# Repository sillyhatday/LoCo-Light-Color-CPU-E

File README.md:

# Introduction

As you may know, there are different revision CPUs that came in the GBC. All are compatible with each other except the last revision. This project allows for the use of that version inside of a Gameboy Light form factor.

The final revision CGB was cost cut as much as possible, Nintendo removed as much as they could from the console. All filtering removed by Nintendo has been removed from this also.

There is a bit of shell trimming required when assembling. The front face of the shell requires trimming for the screen like all IPS screen replacements. There is some trimming needed around the click wheel also as it's bigger than the orginal contrast wheel on a Light console. I'll document this when I have completed the build.

>[!IMPORTANT]
>This version only works with CGB-CPU-06 revisions, known as CPU-E

>[!NOTE]
>Limited new parts are needed, the 2.5v regulator and toggle wheel. I could have used the regulator from the donor, it just has an odd pin out. Such a small part is easy to loose or damage, so I went with a new part with a standard pin out. Everything else is the same as the original version.

Here is Natalie's origiinal readme with my images.

# LoCo (Light Color) - NatalieTheNerd

LoCo = Light Color. This project allows you to put a Game Boy Color in a Game Boy Light shell. Full Light colour PCB using the original parts. This board is made with modern screen kits in mind meaning it does not have the voltage rails for the original screen.

**ORDER AT 1MM WITH ENIG**

You can support me on Ko-Fi or by buying the board directly from me [my store](https://nataliethenerd.com/collections/all)

I also occasionally sell pre built PCBs on my store.

## Building

> [!WARNING]
> I am not responsible for your skill issues!

>[!TIP]
>Some details that will need your atention during assembly are [here](SHELLTRIMMING.md)

This board uses all the parts of an original Game Boy Color minus the IR and original screen circuit. Most parts are in the same spot, however if you are having trouble you can check the [interactive BOM](https://nataliethenerd.github.io/loco.html)

The thumbwheel circuit can be connected to an OSD screen to control brightness. The two touch pad wires and be connected to the pads labelled ↑↓ on the back top left side of the board. The select, A and B pads are easy connection pads for the screen also. 

**My recommendations** 

- New power regulator like my [Safer Charge DC](https://nataliethenerd.com/products/safer-charge-dc)
- [Q5 OSD Game Boy Color screen](https://s.click.aliexpress.com/e/_DmvDS95). The OSD allows you to move the screen

**New parts**

- [Thumbwheel](https://s.click.aliexpress.com/e/_DFcsKf1)

## Thanks
- Hozy for the pushing me to do the first ever Light Color
- Console and Casks for the thumbwheel circuit

## Follow me

If you are into Game Boy modding or retro gaming, please consider using code "NatalieTheNerd" at:

• [Retro Modding](http://RetroModding.com) 

• [Retro Game Repair Shop](http://RetroGameRepairShop.com) 

• [Extreme Rate](http://ExtremeRate.com)

**My socials**

• [Twitter](https://twitter.com/natalie_thenerd) 

• [BlueSky](https://bsky.app/profile/nataliethenerd.com) 

• [Instagram](https://www.instagram.com/natalie.thenerd/) 

• [Modded Gameboy Club](https://moddedgameboy.club/) - a club dedicated to the modification of Game Boys, freely sharing resources

## License

Please do not remove my logo, website and name.

The CC BY-SA 4.0 (Creative Commons Attribution-ShareAlike 4.0 International) license allows you to:

1. **Share** - Copy and redistribute the material in any medium or format.
2. **Adapt** - Remix, transform, and build upon the material for any purpose, even commercially.

### Conditions:

- **Attribution** - You must give appropriate credit, provide a link to the license, and indicate if changes were made. You may do so in any reasonable manner, but not in any way that suggests the licensor endorses you or your use.
- **ShareAlike** - If you remix, transform, or build upon the material, you must distribute your contributions under the same license as the original.

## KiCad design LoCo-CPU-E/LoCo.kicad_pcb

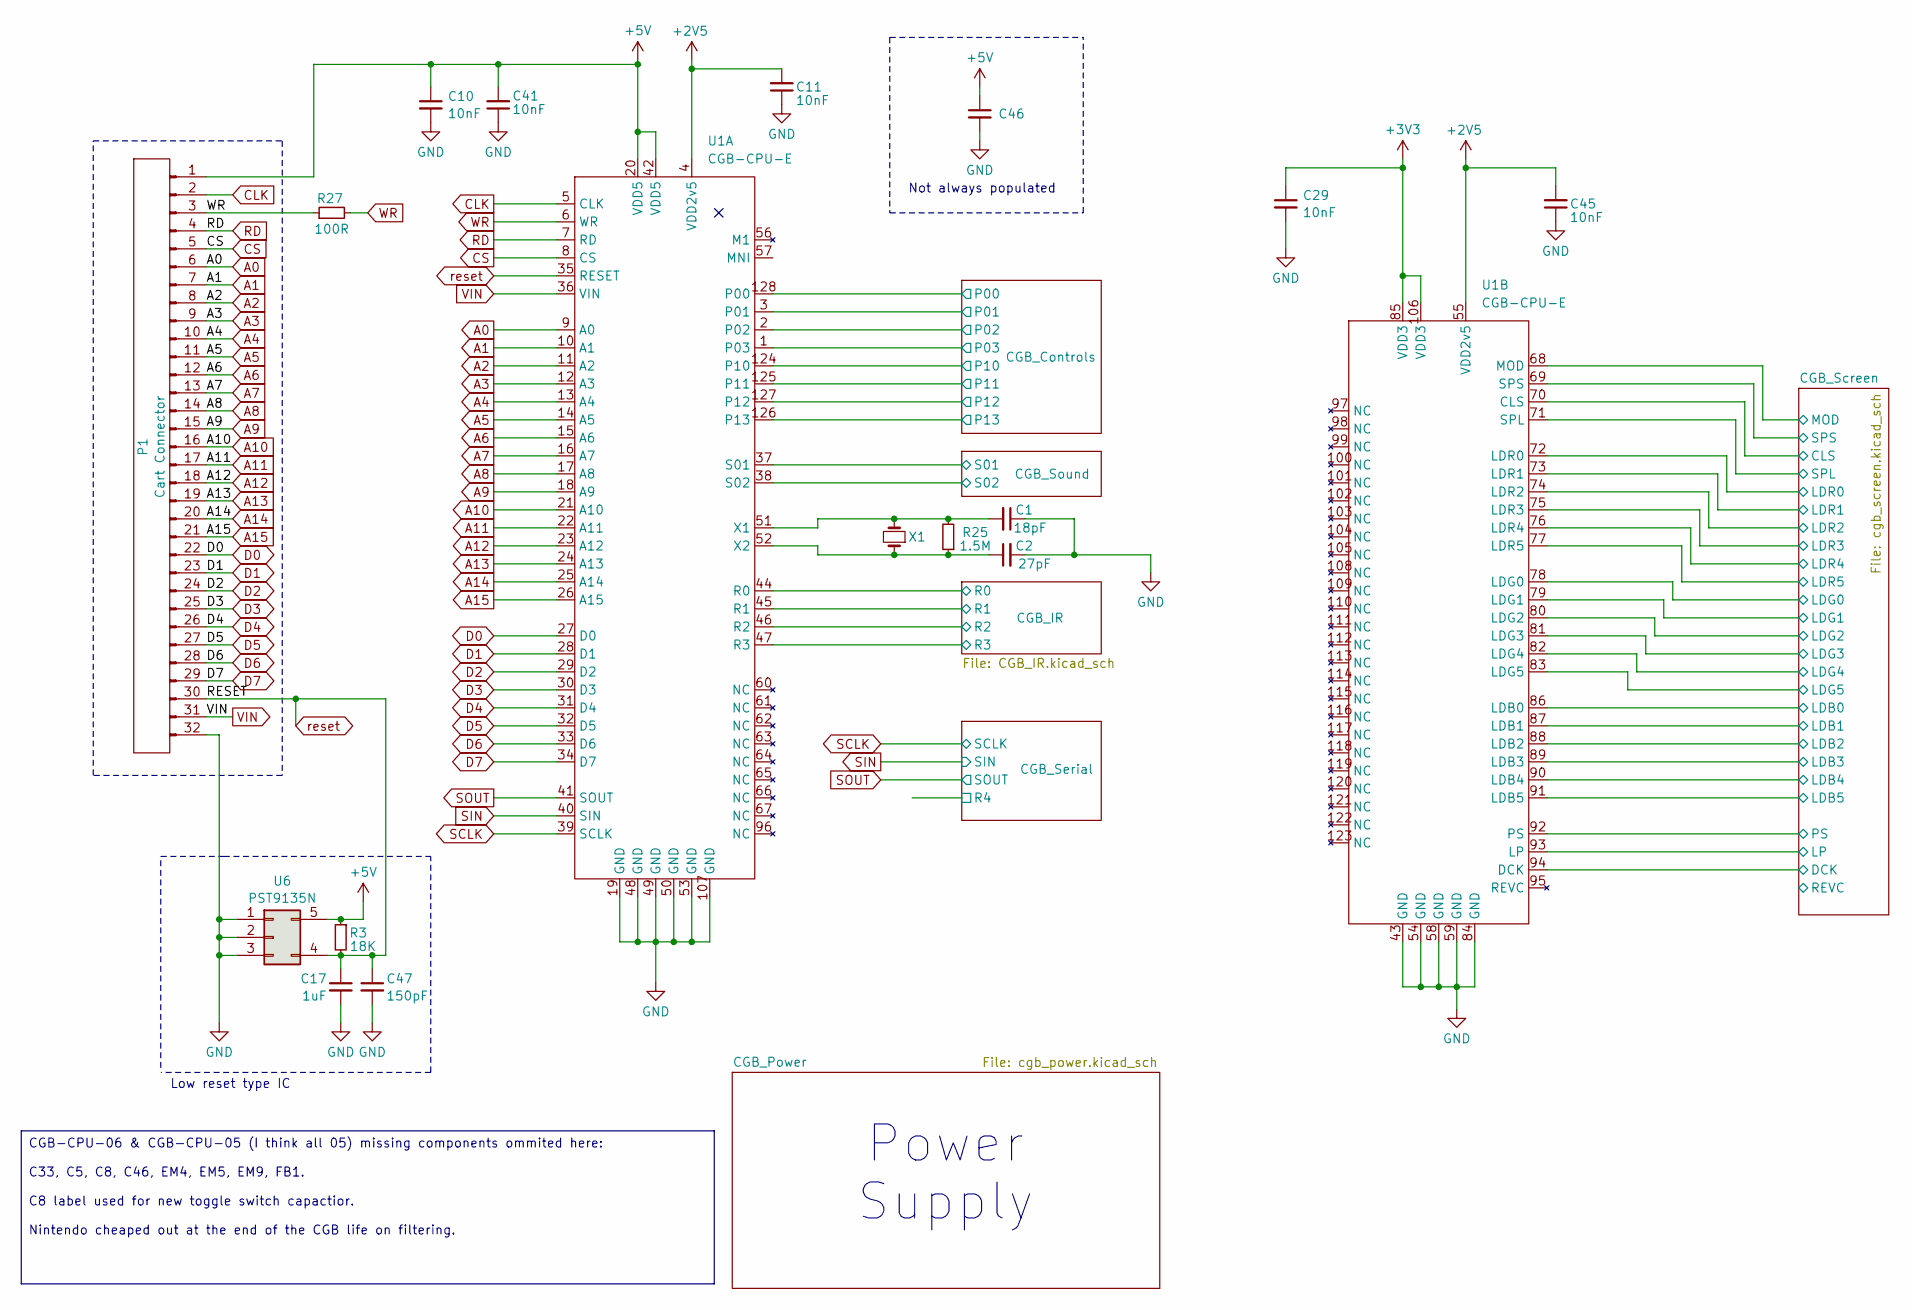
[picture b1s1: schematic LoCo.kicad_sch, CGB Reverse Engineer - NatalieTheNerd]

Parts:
C1: 18pF; C_0603_1608Metric
C2: 27pF; C_0603_1608Metric
C10, C11, C29, C41, C45: 10nF; C_0603_1608Metric
C17: 1uF; C_0603_1608Metric
C46: C_0603_1608Metric
C47: 150pF; C_0603_1608Metric
P1: Cart Connector; Cart CGB
R3: 18K; R_0603_1608Metric
R25: 1.5M; R_0603_1608Metric
R27: 100R; R_0603_1608Metric
U1: CGB-CPU-E; CPU CGB
U6: PST9135N; SOT-23-5
X1: Crystal_Small; Crystal CGB

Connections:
+2V5: C11.2, C45.2, U1.4 (VDD2v5), U1.55 (VDD2v5); also elsewhere on the board
+3V3: C29.1, U1.85 (VDD3), U1.106 (VDD3); also elsewhere on the board
+5V: C10.1, C41.2, C46.1, P1.1, R3.1, U1.20 (VDD5), U1.42 (VDD5), U6.5; also elsewhere on the board
/CGB_Controls/P00: U1.128 (P00); also elsewhere on the board
/CGB_Controls/P01: U1.3 (P01); also elsewhere on the board
/CGB_Controls/P02: U1.2; also elsewhere on the board
/CGB_Controls/P03: U1.1 (P03); also elsewhere on the board
/CGB_Controls/P10: U1.124 (P10); also elsewhere on the board
/CGB_Controls/P11: U1.125 (P11); also elsewhere on the board
/CGB_Controls/P12: U1.127 (P12); also elsewhere on the board
/CGB_Controls/P13: U1.126 (P13); also elsewhere on the board
/CGB_Screen/CLS: U1.70 (CLS); also elsewhere on the board
/CGB_Screen/DCK: U1.94 (DCK); also elsewhere on the board
/CGB_Screen/LDB0: U1.86 (LDB0); also elsewhere on the board
/CGB_Screen/LDB1: U1.87 (LDB1); also elsewhere on the board
/CGB_Screen/LDB2: U1.88 (LDB2); also elsewhere on the board
/CGB_Screen/LDB3: U1.89 (LDB3); also elsewhere on the board
/CGB_Screen/LDB4: U1.90 (LDB4); also elsewhere on the board
/CGB_Screen/LDB5: U1.91 (LDB5); also elsewhere on the board
/CGB_Screen/LDG0: U1.78 (LDG0); also elsewhere on the board
/CGB_Screen/LDG1: U1.79 (LDG1); also elsewhere on the board
/CGB_Screen/LDG2: U1.80 (LDG2); also elsewhere on the board
/CGB_Screen/LDG3: U1.81 (LDG3); also elsewhere on the board
/CGB_Screen/LDG4: U1.82 (LDG4); also elsewhere on the board
/CGB_Screen/LDG5: U1.83 (LDG5); also elsewhere on the board
/CGB_Screen/LDR0: U1.72 (LDR0); also elsewhere on the board
/CGB_Screen/LDR1: U1.73 (LDR1); also elsewhere on the board
/CGB_Screen/LDR2: U1.74 (LDR2); also elsewhere on the board
/CGB_Screen/LDR3: U1.75 (LDR3); also elsewhere on the board
/CGB_Screen/LDR4: U1.76 (LDR4); also elsewhere on the board
/CGB_Screen/LDR5: U1.77 (LDR5); also elsewhere on the board
/CGB_Screen/LP: U1.93 (LP); also elsewhere on the board
/CGB_Screen/MOD: U1.68 (MOD); also elsewhere on the board
/CGB_Screen/PS: U1.92 (PS); also elsewhere on the board
/CGB_Screen/SPL: U1.71 (SPL); also elsewhere on the board
/CGB_Screen/SPS: U1.69 (SPS); also elsewhere on the board
/CGB_Sound/S01: U1.37 (S01); also elsewhere on the board
/CGB_Sound/S02: U1.38 (S02); also elsewhere on the board
/R0: U1.44 (R0)
/R1: U1.45 (R1)
/R2: U1.46 (R2)
/R3: U1.47 (R3)
A0: P1.6, U1.9 (A0)
A1: P1.7, U1.10 (A1)
A2: P1.8, U1.11 (A2)
A3: P1.9, U1.12 (A3)
A4: P1.10, U1.13 (A4)
A5: P1.11, U1.14 (A5)
A6: P1.12, U1.15 (A6)
A7: P1.13, U1.16 (A7)
A8: P1.14, U1.17 (A8)
A9: P1.15, U1.18 (A9)
A10: P1.16, U1.21 (A10)
A11: P1.17, U1.22 (A11)
A12: P1.18, U1.23 (A12)
A13: P1.19, U1.24 (A13)
A14: P1.20, U1.25 (A14)
A15: P1.21, U1.26 (A15)
CLK: P1.2, U1.5 (CLK)
CS: P1.5, U1.8 (CS)
D0: P1.22, U1.27 (D0)
D1: P1.23, U1.28 (D1)
D2: P1.24, U1.29 (D2)
D3: P1.25, U1.30 (D3)
D4: P1.26, U1.31 (D4)
D5: P1.27, U1.32 (D5)
D6: P1.28, U1.33 (D6)
D7: P1.29, U1.34 (D7)
GND: C1.1, C2.2, C10.2, C11.1, C17.2, C29.2, C41.1, C45.1, C46.2, C47.2, P1.32, U1.19 (GND), U1.43 (GND), U1.48 (GND), U1.49 (GND), U1.50 (GND), U1.53 (GND), U1.54 (GND), U1.58 (GND), U1.59 (GND), U1.84 (GND), U1.107 (GND), U6.1, U6.2, U6.3; also elsewhere on the board
unnamed: C1.2, R25.2, U1.51 (X1), X1.2
unnamed: C2.1, R25.1, U1.52 (X2), X1.1
RD: P1.4, U1.7 (RD)
SCLK: U1.39 (SCLK); also elsewhere on the board
SIN: U1.40 (SIN); also elsewhere on the board
SOUT: U1.41 (SOUT); also elsewhere on the board
VIN: P1.31, U1.36 (VIN)
WR: P1.3, R27.1, R27.2, U1.6 (WR)
reset: C17.1, C47.1, P1.30, R3.2, U1.35 (RESET), U6.4; also elsewhere on the board

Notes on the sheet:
Not always populated
Power Supply
Low reset type IC
CGB-CPU-06 & CGB-CPU-05 (I think all 05) missing components ommited here: C33, C5, C8, C46, EM4, EM5, EM9, FB1. C8 label used for new toggle switch capactior. Nintendo cheaped out at the end of the CGB life on filtering.

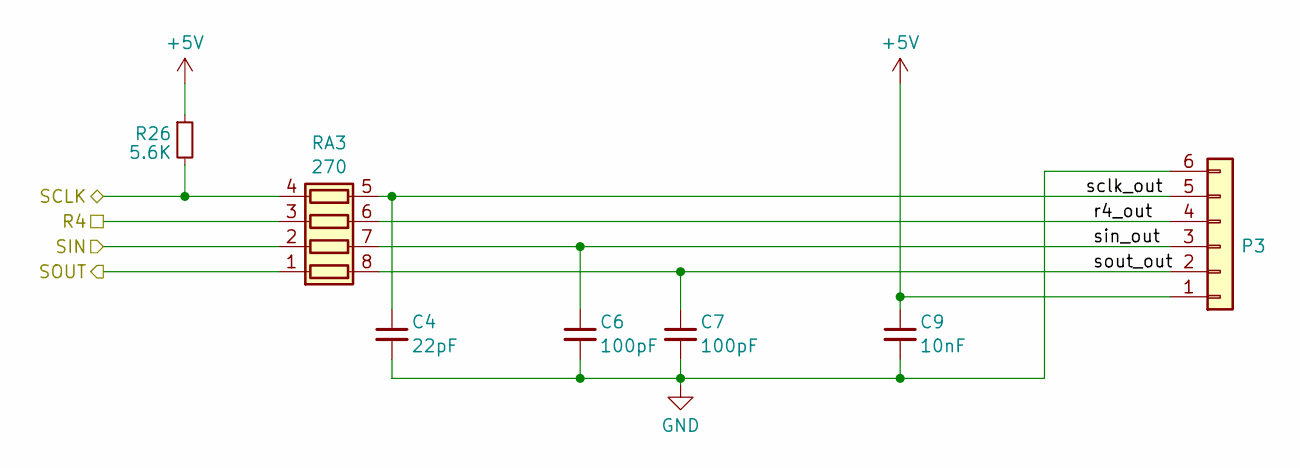
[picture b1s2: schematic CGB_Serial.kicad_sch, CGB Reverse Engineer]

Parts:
C4: 22pF; C_0603_1608Metric
C6, C7: 100pF; C_0603_1608Metric
C9: 10nF; C_0603_1608Metric
P3: Conn_01x06; Serial CGB
R26: 5.6K; R_0603_1608Metric
RA3: 270; R_Array_Concave_4x0603

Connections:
+5V: C9.1, P3.1, R26.1; also elsewhere on the board
/CGB_Serial/R4: RA3.3 (R3.1)
/CGB_Serial/r4_out: P3.4, RA3.6 (R3.2)
/CGB_Serial/sclk_out: C4.1, P3.5, RA3.5 (R4.2)
/CGB_Serial/sin_out: C6.1, P3.3, RA3.7 (R2.2)
/CGB_Serial/sout_out: C7.1, P3.2, RA3.8 (R1.2)
GND: C4.2, C6.2, C7.2, C9.2, P3.6; also elsewhere on the board
SCLK: R26.2, RA3.4 (R4.1); also elsewhere on the board
SIN: RA3.2 (R2.1); also elsewhere on the board
SOUT: RA3.1 (R1.1); also elsewhere on the board

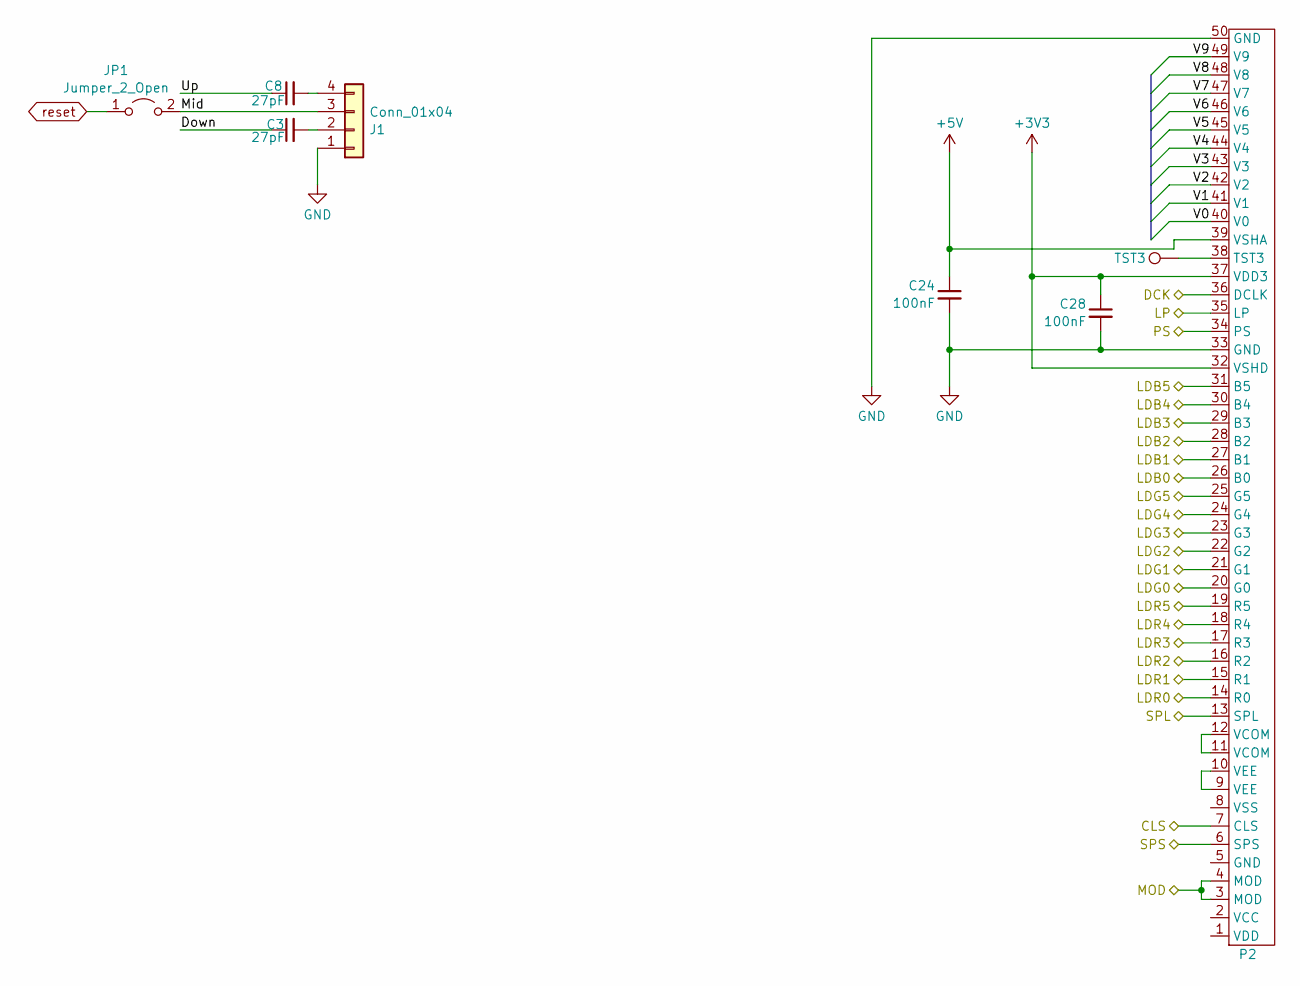
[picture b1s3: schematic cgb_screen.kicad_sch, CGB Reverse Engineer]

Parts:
C3, C8: 27pF; R_0603_1608Metric
C24, C28: 100nF; C_0603_1608Metric
J1: Conn_01x04; Thumbwheel toggle switch
JP1: Jumper_2_Open; SolderJumper-2_P1.3mm_Open_RoundedPad1.0x1.5mm
P2: Screen CGB
TST3: TestPoint

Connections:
+3V3: C28.1, P2.32 (VSHD), P2.37 (VDD3); also elsewhere on the board
+5V: C24.1, P2.39 (VSHA); also elsewhere on the board
/CGB_Screen/CLS: P2.7 (CLS); also elsewhere on the board
/CGB_Screen/DCK: P2.36 (DCLK); also elsewhere on the board
/CGB_Screen/Down: C3.1
/CGB_Screen/LDB0: P2.26 (B0); also elsewhere on the board
/CGB_Screen/LDB1: P2.27 (B1); also elsewhere on the board
/CGB_Screen/LDB2: P2.28 (B2); also elsewhere on the board
/CGB_Screen/LDB3: P2.29 (B3); also elsewhere on the board
/CGB_Screen/LDB4: P2.30 (B4); also elsewhere on the board
/CGB_Screen/LDB5: P2.31 (B5); also elsewhere on the board
/CGB_Screen/LDG0: P2.20 (G0); also elsewhere on the board
/CGB_Screen/LDG1: P2.21 (G1); also elsewhere on the board
/CGB_Screen/LDG2: P2.22 (G2); also elsewhere on the board
/CGB_Screen/LDG3: P2.23 (G3); also elsewhere on the board
/CGB_Screen/LDG4: P2.24 (G4); also elsewhere on the board
/CGB_Screen/LDG5: P2.25 (G5); also elsewhere on the board
/CGB_Screen/LDR0: P2.14 (R0); also elsewhere on the board
/CGB_Screen/LDR1: P2.15 (R1); also elsewhere on the board
/CGB_Screen/LDR2: P2.16 (R2); also elsewhere on the board
/CGB_Screen/LDR3: P2.17 (R3); also elsewhere on the board
/CGB_Screen/LDR4: P2.18 (R4); also elsewhere on the board
/CGB_Screen/LDR5: P2.19 (R5); also elsewhere on the board
/CGB_Screen/LP: P2.35 (LP); also elsewhere on the board
/CGB_Screen/MOD: P2.3 (MOD), P2.4 (MOD); also elsewhere on the board
/CGB_Screen/Mid: J1.3, JP1.2 (B)
/CGB_Screen/PS: P2.34 (PS); also elsewhere on the board
/CGB_Screen/SPL: P2.13 (SPL); also elsewhere on the board
/CGB_Screen/SPS: P2.6 (SPS); also elsewhere on the board
/CGB_Screen/Up: C8.1
/CGB_Screen/V0: P2.40 (V0)
/CGB_Screen/V1: P2.41 (V1)
/CGB_Screen/V2: P2.42 (V2)
/CGB_Screen/V3: P2.43 (V3)
/CGB_Screen/V4: P2.44 (V4)
/CGB_Screen/V5: P2.45 (V5)
/CGB_Screen/V6: P2.46 (V6)
/CGB_Screen/V7: P2.47 (V7)
/CGB_Screen/V8: P2.48 (V8)
/CGB_Screen/V9: P2.49 (V9)
GND: C24.2, C28.2, J1.1, P2.33 (GND), P2.50 (GND); also elsewhere on the board
unnamed: C3.2, J1.2
unnamed: C8.2, J1.4
unnamed: P2.38 (TST3), TST3.1
unnamed: P2.11 (VCOM), P2.12 (VCOM)
unnamed: P2.9 (VEE), P2.10 (VEE)
reset: JP1.1 (A); also elsewhere on the board

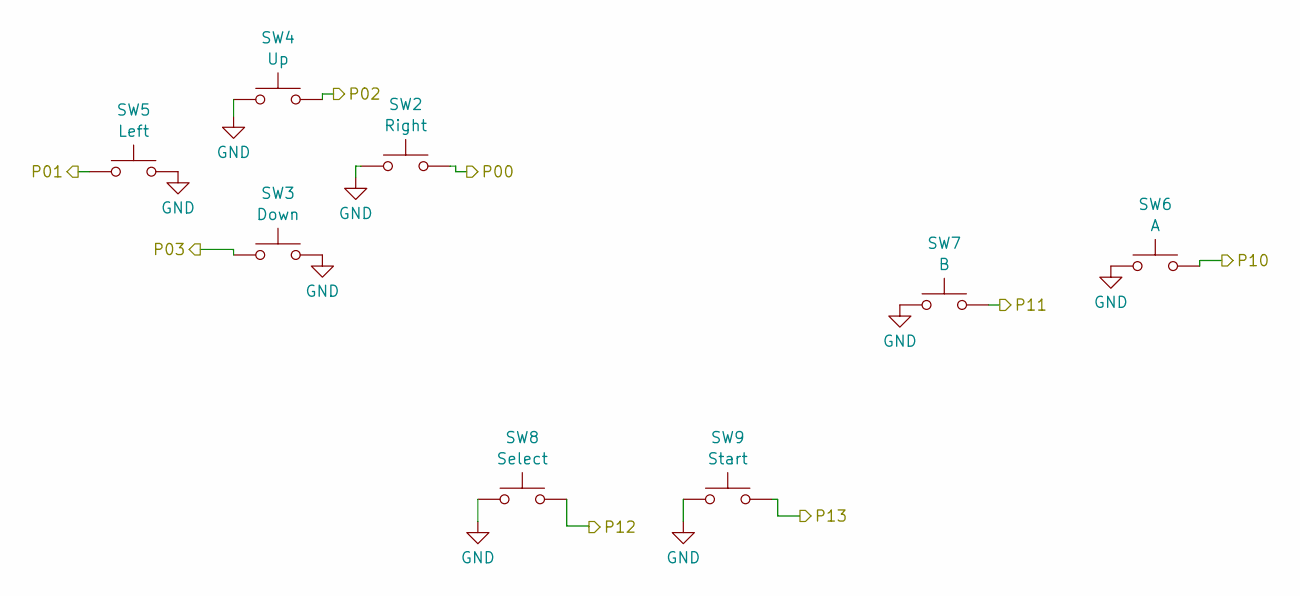
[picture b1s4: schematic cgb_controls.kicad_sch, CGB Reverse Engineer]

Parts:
SW2: Right; Dpad CGB
SW3: Down; Dpad CGB
SW4: Up; Dpad CGB
SW5: Left; Dpad CGB
SW6: A; AB CGB
SW7: B; AB CGB
SW8: Select; Select CGB
SW9: Start; Start CGB

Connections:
/CGB_Controls/P00: SW2.2; also elsewhere on the board
/CGB_Controls/P01: SW5.1; also elsewhere on the board
/CGB_Controls/P02: SW4.2; also elsewhere on the board
/CGB_Controls/P03: SW3.1; also elsewhere on the board
/CGB_Controls/P10: SW6.2; also elsewhere on the board
/CGB_Controls/P11: SW7.2; also elsewhere on the board
/CGB_Controls/P12: SW8.2; also elsewhere on the board
/CGB_Controls/P13: SW9.2; also elsewhere on the board
GND: SW2.1, SW3.2, SW4.1, SW5.2, SW6.1, SW7.1, SW8.1, SW9.1; also elsewhere on the board

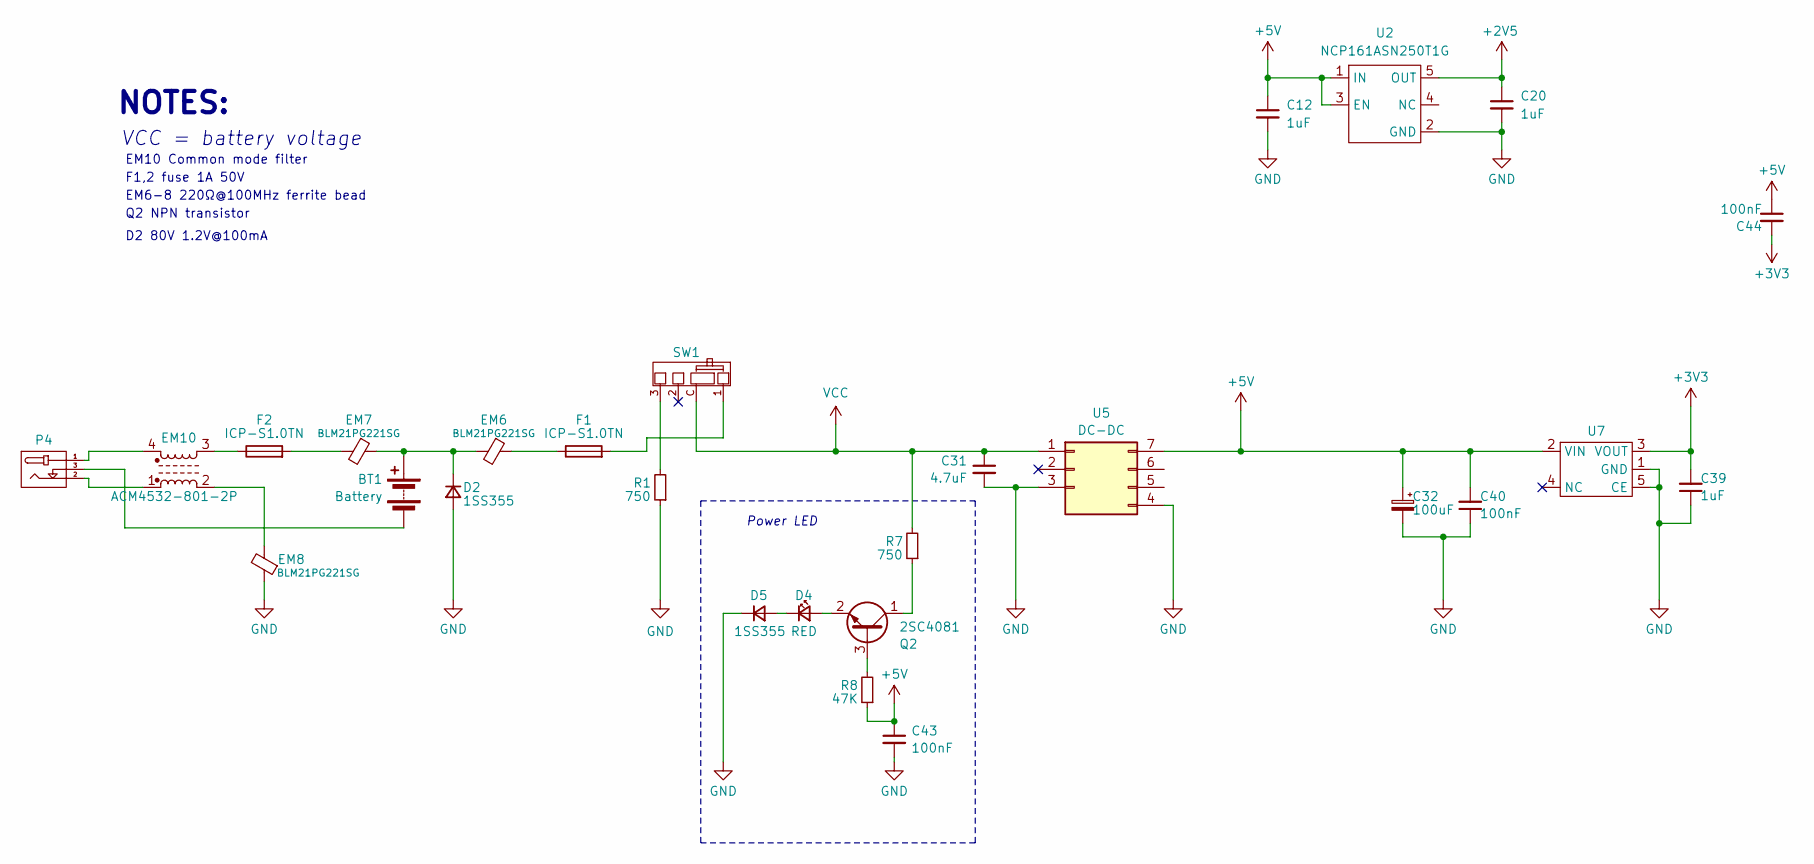
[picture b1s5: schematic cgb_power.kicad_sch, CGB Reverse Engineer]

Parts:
BT1: Battery; Battery CGB
C12, C20, C39: 1uF; C_0603_1608Metric
C31: 4.7uF; C_0603_1608Metric
C32: 100uF; CP_Elec_6.3x5.4
C40, C43, C44: 100nF; C_0603_1608Metric
D2, D5: 1SS355; D_SOD-323_HandSoldering
D4: RED; LED_D3.0mm
EM6, EM7, EM8: BLM21PG221SG; R_0805_2012Metric
EM10: ACM4532-801-2P; Crystal_SMD_EuroQuartz_MJ-4Pin_5.0x3.2mm
F1, F2: ICP-S1.0TN; Fuse_1206_3216Metric_Pad1.42x1.75mm_HandSolder
P4: DCJACK
Q2: 2SC4081; SOT-323_SC-70
R1, R7: 750; R_0603_1608Metric
R8: 47K; R_0603_1608Metric
SW1: Switch CGB
U2: NCP161ASN250T1G; SOT-23-5
U5: DC-DC; DC
U7: SOT-23-5

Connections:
+2V5: C20.1, U2.5 (OUT); also elsewhere on the board
+3V3: C39.2, C44.2, U7.3 (VOUT); also elsewhere on the board
+5V: C12.1, C32.1, C40.2, C43.1, C44.1, R8.1, U2.1 (IN), U2.3 (EN), U5.7, U7.2 (VIN); also elsewhere on the board
GND: C12.2, C20.2, C31.2, C32.2, C39.1, C40.1, C43.2, D2.2 (A), D5.1 (K), EM8.1, R1.1, U2.2 (GND), U5.3, U5.4, U7.1 (GND), U7.5 (CE); also elsewhere on the board
unnamed: BT1.1 (+), D2.1 (K), EM6.2, EM7.1
unnamed: BT1.2 (-), P4.3
unnamed: D4.2 (A), Q2.2 (B)
unnamed: D4.1 (K), D5.2 (A)
unnamed: EM6.1, F1.1
unnamed: EM7.2, F2.2
unnamed: EM10.1, P4.2
unnamed: EM8.2, EM10.2
unnamed: EM10.3, F2.1
unnamed: EM10.4, P4.1
unnamed: F1.2, SW1.1
unnamed: Q2.3 (C), R8.2
unnamed: Q2.1 (E), R7.1
unnamed: R1.2, SW1.3
VCC: C31.1, R7.2, SW1.C, U5.1; also elsewhere on the board

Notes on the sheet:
NOTES:
D2 80V 1.2V@100mA
EM6-8 220Ω@100MHz ferrite bead
EM10 Common mode filter
F1,2 fuse 1A 50V
Power LED
Q2 NPN transistor
VCC = battery voltage

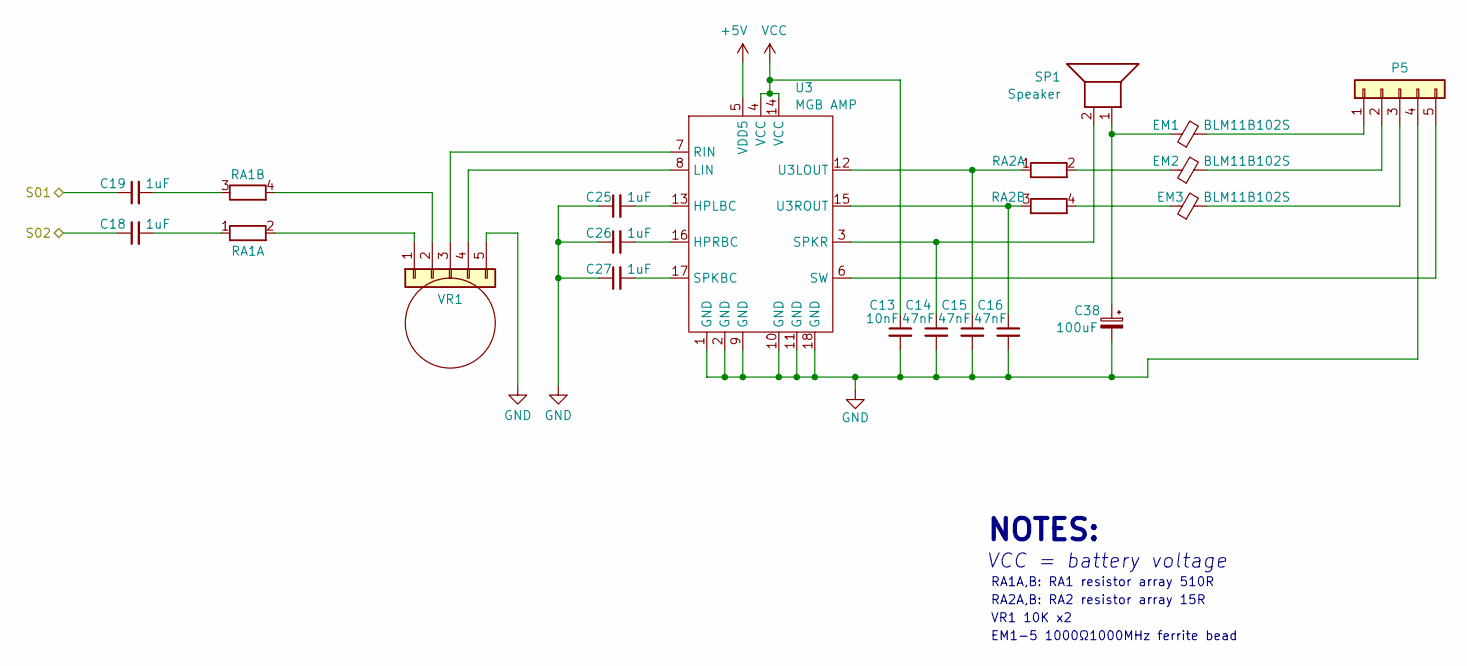
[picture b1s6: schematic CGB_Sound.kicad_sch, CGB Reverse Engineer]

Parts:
C13: 10nF; C_0603_1608Metric
C14, C15, C16: 47nF; C_0603_1608Metric
C18, C19, C25, C26, C27: 1uF; C_0603_1608Metric
C38: 100uF; CP_Elec_5x5.3
EM1, EM2, EM3: BLM11B102S; R_0603_1608Metric
P5: Conn_01x05; HPjack
RA1, RA2: R_Pack02_SIP_Split; R_Array_Concave_2x0603
SP1: Speaker; TestPoint_2Pads_Pitch2.54mm_Drill0.8mm
U3: MGB AMP; Amp MGB
VR1: Conn_01x05; Volume wheel CGB

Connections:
+5V: U3.5 (VDD5); also elsewhere on the board
/CGB_Sound/S01: C19.1; also elsewhere on the board
/CGB_Sound/S02: C18.1; also elsewhere on the board
GND: C13.2, C14.2, C15.2, C16.2, C25.1, C26.1, C27.1, C38.2, P5.4, U3.1 (GND), U3.2 (GND), U3.9 (GND), U3.10 (GND), U3.11 (GND), U3.18 (GND), VR1.5; also elsewhere on the board
unnamed: C38.1, EM1.1, SP1.1
unnamed: EM1.2, P5.1
unnamed: EM2.2, P5.2
unnamed: EM3.2, P5.3
unnamed: P5.5, U3.6 (SW)
unnamed: C18.2, RA1.1 (R1.1)
unnamed: RA1.2 (R1.2), VR1.1
unnamed: C19.2, RA1.3 (R2.1)
unnamed: RA1.4 (R2.2), VR1.2
unnamed: C15.1, RA2.1 (R1.1), U3.12 (U3LOUT)
unnamed: EM2.1, RA2.2 (R1.2)
unnamed: C16.1, RA2.3 (R2.1), U3.15 (U3ROUT)
unnamed: EM3.1, RA2.4 (R2.2)
unnamed: C25.2, U3.13 (HPLBC)
unnamed: C26.2, U3.16 (HPRBC)
unnamed: U3.8 (LIN), VR1.4
unnamed: U3.7 (RIN), VR1.3
unnamed: C27.2, U3.17 (SPKBC)
unnamed: C14.1, SP1.2, U3.3 (SPKR)
VCC: C13.1, U3.4 (VCC), U3.14 (VCC); also elsewhere on the board

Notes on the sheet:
EM1-5 1000Ω1000MHz ferrite bead
RA1A,B: RA1 resistor array 510R
VR1 10K x2
VCC = battery voltage
NOTES:
RA2A,B: RA2 resistor array 15R

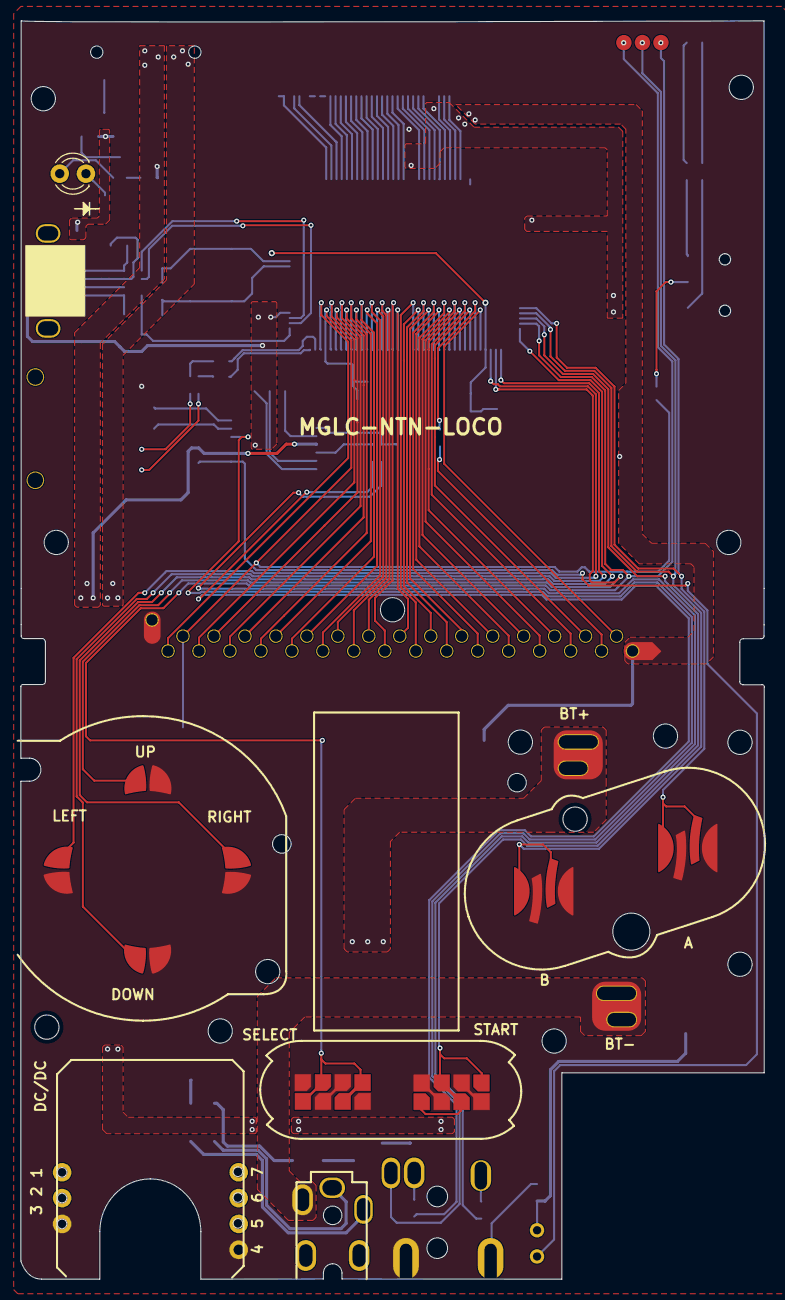
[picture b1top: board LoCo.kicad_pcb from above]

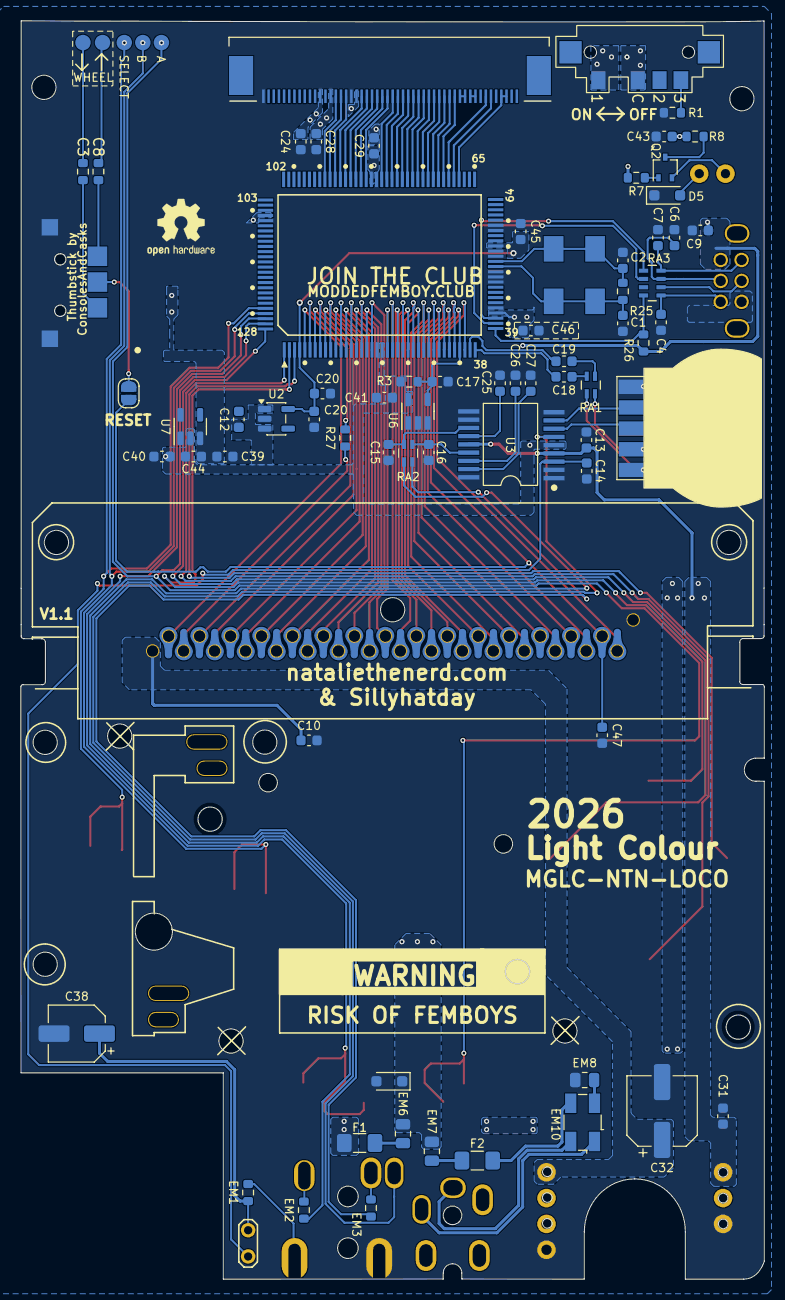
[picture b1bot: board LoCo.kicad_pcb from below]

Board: 2 copper layers, 71.9 x 121.8 mm, 85 parts (70 on the bottom side), 117 nets.

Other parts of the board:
C20#2: 1uF; C_0603_1608Metric

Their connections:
+2V5: C20#2.1; also elsewhere on the board
GND: C20#2.2; also elsewhere on the board

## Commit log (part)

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2025-12-08 Create KiCad-Loco-CPU-E
2025-12-08 Design files uploaded
2025-12-08 Gerbers uploaded
2025-12-08 Update README.md
    Added preface
2025-12-09 Add files via upload
    pinout diagram added
2026-06-16 Update README.md
    Updated readme after initial prototype build
2026-06-16 Delete KiCad-Loco-CPU-E directory
    Removed original kicad files
2026-06-16 Create dummy.md
    dummy
2026-06-16 Add files via upload
    new kicad files
2026-06-16 Add files via upload
    added gerbers
2026-06-26 Update README.md
    brief about shell trimming
2026-06-26 Update README.md
    typo fixed from yesterday
2026-06-28 Update README.md
    pre shell trimming guide
2026-06-28 Update README.md
    added link
